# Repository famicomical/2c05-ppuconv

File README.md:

# 2c05-ppuconv
Allows 2C05 PPU chips to interface with an NES motherboard to get RGB video. 

The RC2C05 chips contain fewer glitches than the the RP2C03B chips normally used for the mod, but they have the drawback of not being directly connectable to an NES motherboard. this project solves that problem. Of course, [viletim's NESRGB kit](http://etim.net.au/nesrgb/) will give better results for an RGB mod and is generally the preferred RGB upgrade method, but this project remains of interest to those who want to mod their NES the ['old-fashioned'](nesrgbold.png) way.

the logic circuit takes after the one in the schematic shown below.

refer to [nesdev wiki](https://www.nesdev.org/wiki/PPU_pinout) for the PPU pinout mentioned in the following guide.
## Install Guide:

- After removing the original 2C02 PPU and installing a DIP-40 socket in its place, cut the trace leading PPU pin 12 (CPU A0) to the motherboard. 
- Solder the assembled 2c05-ppuconv PCB to the backside of the PPU socket on the Famicom/NES motherboard. Pins A2-out of the 2c05-ppuconv correspond to pins 10-12 on the PPU socket. 
- Scrape some solder mask away from the CPU A0 trace which was cut earlier and solder a wire between there and Pad A0 on the ppuconv. 
- Connect power and ground to the ppuconv PCB. 
- Install the RC2C05 PPU in the socket. Done.

Note: trace cutting is preferred to lifting of the 2C05 PPU pin because the PPU's are a more precious commodity than NES /Famicom motherboards.

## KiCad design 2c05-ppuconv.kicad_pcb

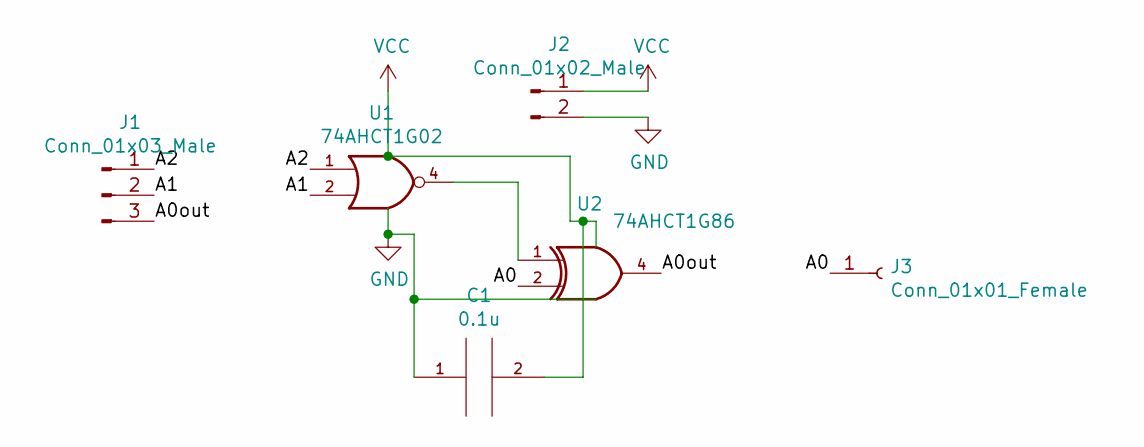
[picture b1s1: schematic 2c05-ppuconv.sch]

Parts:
C1: 0.1u; C_0805_2012Metric_Pad1.15x1.40mm_HandSolder
J1: Conn_01x03_Male; PinHeader_1x03_P2.54mm_Vertical
J2: Conn_01x02_Male; PinHeader_1x02_P2.00mm_Vertical
J3: Conn_01x01_Female; PinHeader_1x01_P2.00mm_Horizontal
U1: 74AHCT1G02; SOT-23-5_HandSoldering
U2: 74AHCT1G86; SOT-23-5_HandSoldering

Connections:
/A0: J3.1, U2.2
/A0out: J1.3, U2.4
/A1: J1.2, U1.2
/A2: J1.1, U1.1
GND: C1.1, J2.2, U1.3 (GND), U2.3 (GND)
unnamed: U1.4, U2.1
VCC: C1.2, J2.1, U1.5 (VCC), U2.5 (VCC)

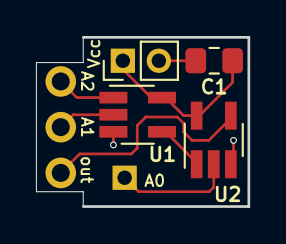
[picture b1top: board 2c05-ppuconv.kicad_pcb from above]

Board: 2 copper layers, 11.7 x 9.4 mm, 6 parts (0 on the bottom side), 7 nets.

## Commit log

2021-08-24 upload project to github
2023-03-04 update documentation, swap A0 and out pins on PCB, shrink PCB
2023-03-04 update figure
2023-03-04 add old-fashion mod guide
